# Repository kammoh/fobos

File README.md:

FOBOS
=====

Flexible Open-source workBench fOr Side-channel analysis (FOBOS) is an "acquisition to analysis" solution which includes all necessary software to control the device under test (attack) (DUT), trigger the oscilloscope, obtain the measurements and analyze them using several power analysis techniques.

FOBOS splits the Side Channel Analysis (SCA) setup into a control board, a DUT, and the SCA workstation. The firmware for the control board can be found in the folder `control`. The hardware description language files required to adapt a cryptographic algorithm to a particular FOBOS DUT are in the folder `DUT`. The `hardware` folder on the other hand contains circuit board design files for FOBOS boards such as the FOBOS Shield and several FOBOS DUTs. The `software` folder contains the scripts to run FOBOS. These python scripts run partially on the SCA workstation within a Jupyter notebook and partially on the Pynq DUT. The `docs` folder contains the FOBOS documentation.

FOBOS Control Board
-------------------
* `control`
   VHDL sources for configuring the FOBOS Control Boards. Requires Xilinx Vivado 2020.2.
   * `basys3ctrl`
     Using a Digilent Inc Basys 3 as control board and an oscilloscope for measurements.
   * `pynqctrl`
     Using a Digilent Inc PYNQ-Z1 as control board and either the FOBOS Shield or an oscilloscope for measurements.
   * `ip-repo` 
     Modules used by either control board.

FOBOS DUT
---------
* `dut`
  VHDL sources for FOBOS wrapper and pin assignments to prepare a DUT for instantiating a target algorithm.
  * `fpga_wrapper`
    Source code of the FOBOS wrapper common to all FPGA targets and the contraint files for the supported DUTs.
  * `soc_wrapper`
    Source code for system on chip boards such as Zybo.
  * `example_cores`
    Contains implementations of example algorithms required for the tutorials.
 
FOBOS Hardware
--------------
* `hardware`
  Printed Circuit Board design files for FOBOS boards. Requires KiCad.
  * `fobos-shield`
    FOBOS Shield is a data aqcuisition and benchmarking boad that can be attached to the PYNQ-Z1 controller.
  * `fobos-mtc`
    FOBOS Multi Target Connector allows simple connection of several DUT boards to the FOBOS Shield.
  * `fobos-dut`
    Contains folders for each FOBOS DUT.

FOBOS Software
--------------
* `software`
  FOBOS is controlled by a series of Python 3 scripts. They can be executed in several different ways.
  1. Command line, either on PYNQ or on a PC, tested on Windows 10 and Linux.
  1. Jupyter Notebook, either on PYNQ or on a PC, tested on Windows 10 and Linux.

  * `foboslib` contains all common FOBOS functions.
  * `notebooks` contains Jupyter notebooks that run within Jypyter Lab on a PC.
  * `pynq=notebooks` contains Jupyter notebooks that run on within Jupyter Hub on Pynq.
  * `examples` contains command line examples

Documentation
-------------

* `docs` 
  Contains the sources for the Sphinx based documentation of FOBOS and the makefile to compile it.
  All figures used for the FOBOS documentation are in the folder `docs\source\figures`.

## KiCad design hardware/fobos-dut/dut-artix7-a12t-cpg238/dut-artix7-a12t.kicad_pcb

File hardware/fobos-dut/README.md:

FOBOS-DUT Boards
=========
  * `dut-spartan7-s15`
    FOBOS DUT with a Xilinx Spartan-7 xc7s15cpga196-2 device and power measurement circuitry.
  * `dut-artix7-a12t-csg325`
    FOBOS DUT with a Xilinx Artix-7 xc7a12tcsg325 device and power measurement circuitry.
  * `dut-artix7-a12t-cpg238`
    FOBOS DUT with a Xilinx Artix-7 xc7a12tcpg238 device and power measurement circuitry.
  * `dut-cyclone10LP-016`
    FOBOS DUT with an Interl Cyclone 10 LP 10CL016-YU256C6 device and power measurement circuitry.
  * `dut-ecp5-25`
    FOBOS DUT with a Lattice ECP5 LFE5U-25F-6BG381C device and power measurement circuitry.

Check git Wiki

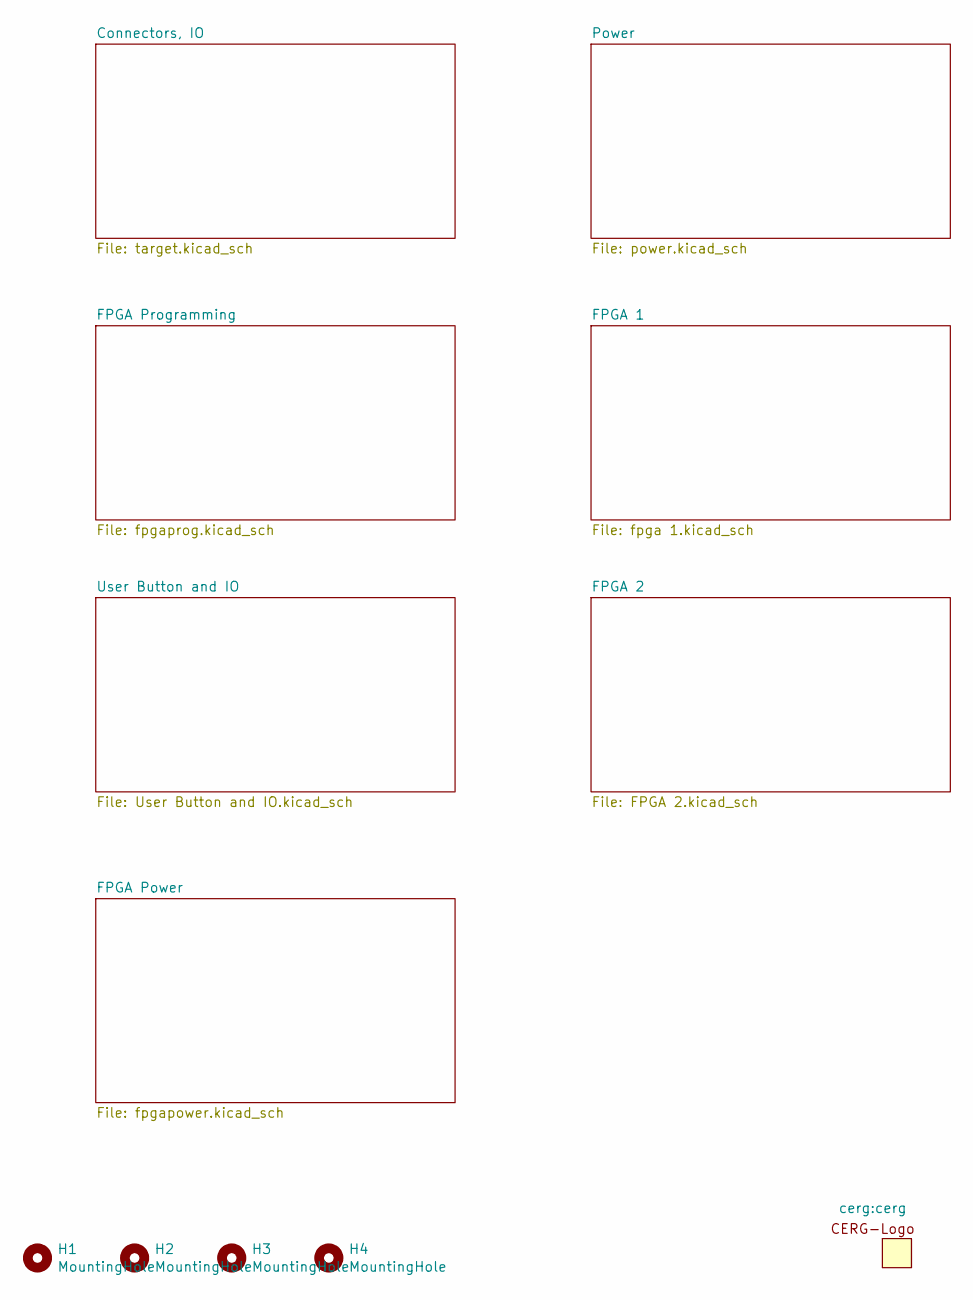
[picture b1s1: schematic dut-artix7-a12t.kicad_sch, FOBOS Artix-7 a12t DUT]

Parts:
H1, H2, H3, H4: MountingHole; MH_4-40

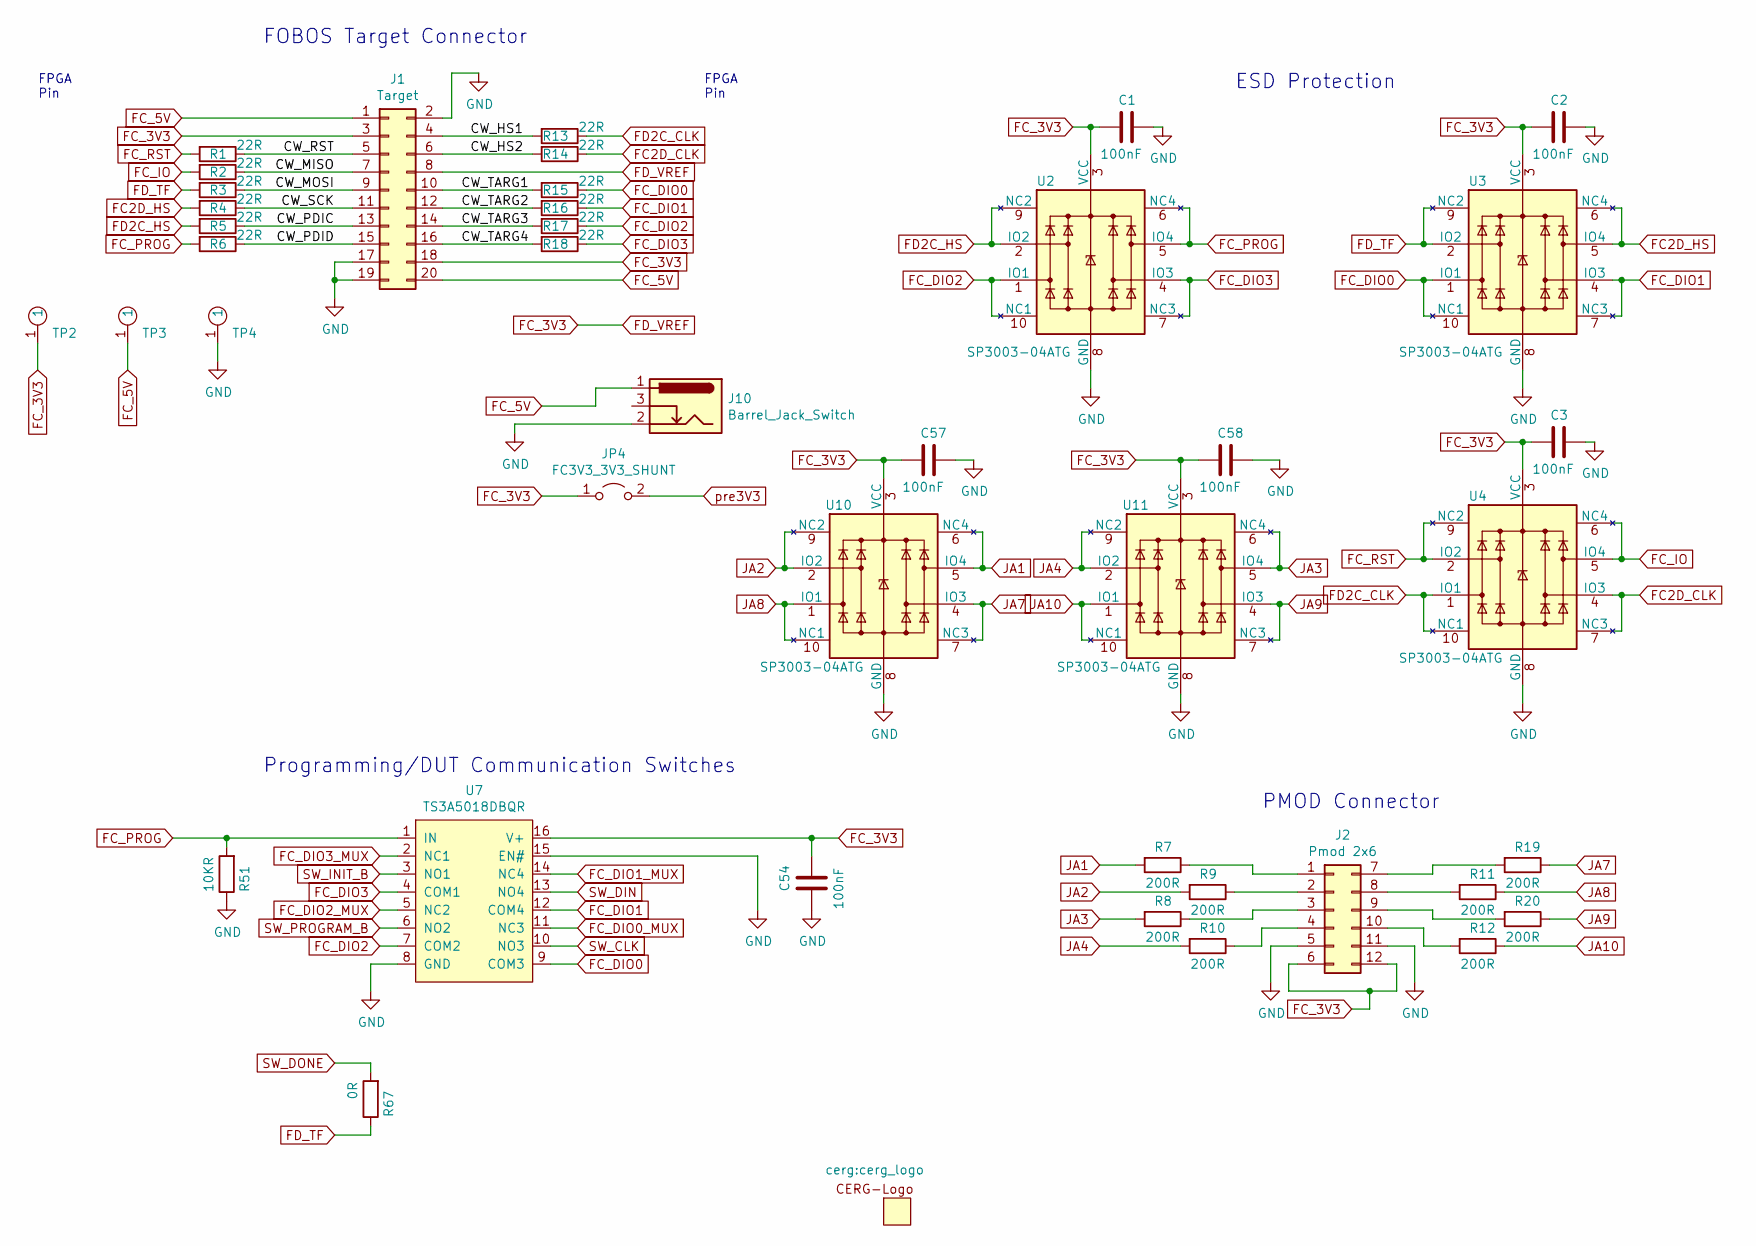
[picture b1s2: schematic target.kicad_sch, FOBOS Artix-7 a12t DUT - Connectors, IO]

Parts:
C1, C2, C3, C54, C57, C58: 100nF; C_0603_1608Metric; MPN 06036C104KAT4A
J1: Target; IDC-Header_2x10_P2.54mm_Horizontal; MPN 61202021721
J2: Pmod 2x6; PinSocket_2x06_P2.54mm_Horizontal_FLipped; MPN PH2RA-12-UA
J10: Barrel_Jack_Switch; BarrelJack_CUI_PJ-102AH_Horizontal
JP4: FC3V3_3V3_SHUNT; PinHeader_1x02_P2.54mm_Vertical; MPN 10129378-902001BLF
R1, R2, R3, R4, R5, R6, R13, R14, R15, R16, R17, R18: 22R; R_0603_1608Metric; MPN ERJ-U03J220V
R7, R8, R9, R10, R11, R12, R19, R20: 200R; R_0603_1608Metric; MPN ERA-3AED201V
R51: 10KR; R_0603_1608Metric; MPN ERJ-3EKF1002V
R67: 0R; R_0603_1608Metric; MPN RMCF0603ZT0R00
TP2, TP3, TP4: 5281; MPN 5281
U2, U3, U4, U10, U11: SP3003-04ATG; MSOP-10_3x3mm_P0.5mm; MPN SP3003-04ATG
U7: TS3A5018DBQR; SSOP-16_4.0x5.0mm_P0.635mm; MPN TS3A5018DBQR

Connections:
/Connectors, IO/CW_HS1: J1.4, R13.2
/Connectors, IO/CW_HS2: J1.6, R14.2
/Connectors, IO/CW_MISO: J1.7, R2.1
/Connectors, IO/CW_MOSI: J1.9, R3.1
/Connectors, IO/CW_PDIC: J1.13, R5.1
/Connectors, IO/CW_PDID: J1.15, R6.1
/Connectors, IO/CW_RST: J1.5, R1.1
/Connectors, IO/CW_SCK: J1.11, R4.1
/Connectors, IO/CW_TARG1: J1.10, R15.2
/Connectors, IO/CW_TARG2: J1.12, R16.2
/Connectors, IO/CW_TARG3: J1.14, R17.2
/Connectors, IO/CW_TARG4: J1.16, R18.2
FC2D_CLK: R14.1, U4.4 (IO3), U4.7 (NC3); also elsewhere on the board
FC2D_HS: R4.2, U3.5 (IO4), U3.6 (NC4); also elsewhere on the board
FC_5V: J1.1, J1.20, J10.1, TP3.1; also elsewhere on the board
FC_DIO0: R15.1, U3.1 (IO1), U3.10 (NC1), U7.9 (COM3)
FC_DIO0_MUX: U7.11 (NC3); also elsewhere on the board
FC_DIO1: R16.1, U3.4 (IO3), U3.7 (NC3), U7.12 (COM4)
FC_DIO1_MUX: U7.14 (NC4); also elsewhere on the board
FC_DIO2: R17.1, U2.1 (IO1), U2.10 (NC1), U7.7 (COM2)
FC_DIO2_MUX: U7.5 (NC2); also elsewhere on the board
FC_DIO3: R18.1, U2.4 (IO3), U2.7 (NC3), U7.4 (COM1)
FC_DIO3_MUX: U7.2 (NC1); also elsewhere on the board
FC_IO: R2.2, U4.5 (IO4), U4.6 (NC4); also elsewhere on the board
FC_PROG: R6.2, R51.2, U2.5 (IO4), U2.6 (NC4), U7.1 (IN)
FC_RST: R1.2, U4.2 (IO2), U4.9 (NC2); also elsewhere on the board
FD2C_CLK: R13.1, U4.1 (IO1), U4.10 (NC1); also elsewhere on the board
FD2C_HS: R5.2, U2.2 (IO2), U2.9 (NC2); also elsewhere on the board
FD_TF: R3.2, R67.1, U3.2 (IO2), U3.9 (NC2)
GND: C1.1, C2.1, C3.1, C54.2, C57.1, C58.1, J1.2, J1.17, J1.19, J2.5, J2.11, J10.2, R51.1, TP4.1, U2.8 (GND), U3.8 (GND), U4.8 (GND), U7.8 (GND), U7.15 (EN#), U10.8 (GND), U11.8 (GND); also elsewhere on the board
JA1: R7.2, U10.5 (IO4), U10.6 (NC4); also elsewhere on the board
JA2: R9.2, U10.2 (IO2), U10.9 (NC2); also elsewhere on the board
JA3: R8.2, U11.5 (IO4), U11.6 (NC4); also elsewhere on the board
JA4: R10.2, U11.2 (IO2), U11.9 (NC2); also elsewhere on the board
JA7: R19.1, U10.4 (IO3), U10.7 (NC3); also elsewhere on the board
JA8: R11.1, U10.1 (IO1), U10.10 (NC1); also elsewhere on the board
JA9: R20.1, U11.4 (IO3), U11.7 (NC3); also elsewhere on the board
JA10: R12.1, U11.1 (IO1), U11.10 (NC1); also elsewhere on the board
unnamed: J2.1, R7.1
unnamed: J2.2, R9.1
unnamed: J2.3, R8.1
unnamed: J2.4, R10.1
unnamed: J2.7, R19.2
unnamed: J2.8, R11.2
unnamed: J2.9, R20.2
unnamed: J2.10, R12.2
SW_CLK: U7.10 (NO3); also elsewhere on the board
SW_DIN: U7.13 (NO4); also elsewhere on the board
SW_DONE: R67.2; also elsewhere on the board
SW_INIT_B: U7.3 (NO1); also elsewhere on the board
SW_PROGRAM_B: U7.6 (NO2); also elsewhere on the board

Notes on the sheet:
Programming/DUT Communication Switches
FPGA Pin
ESD Protection
PMOD Connector
FOBOS Target Connector

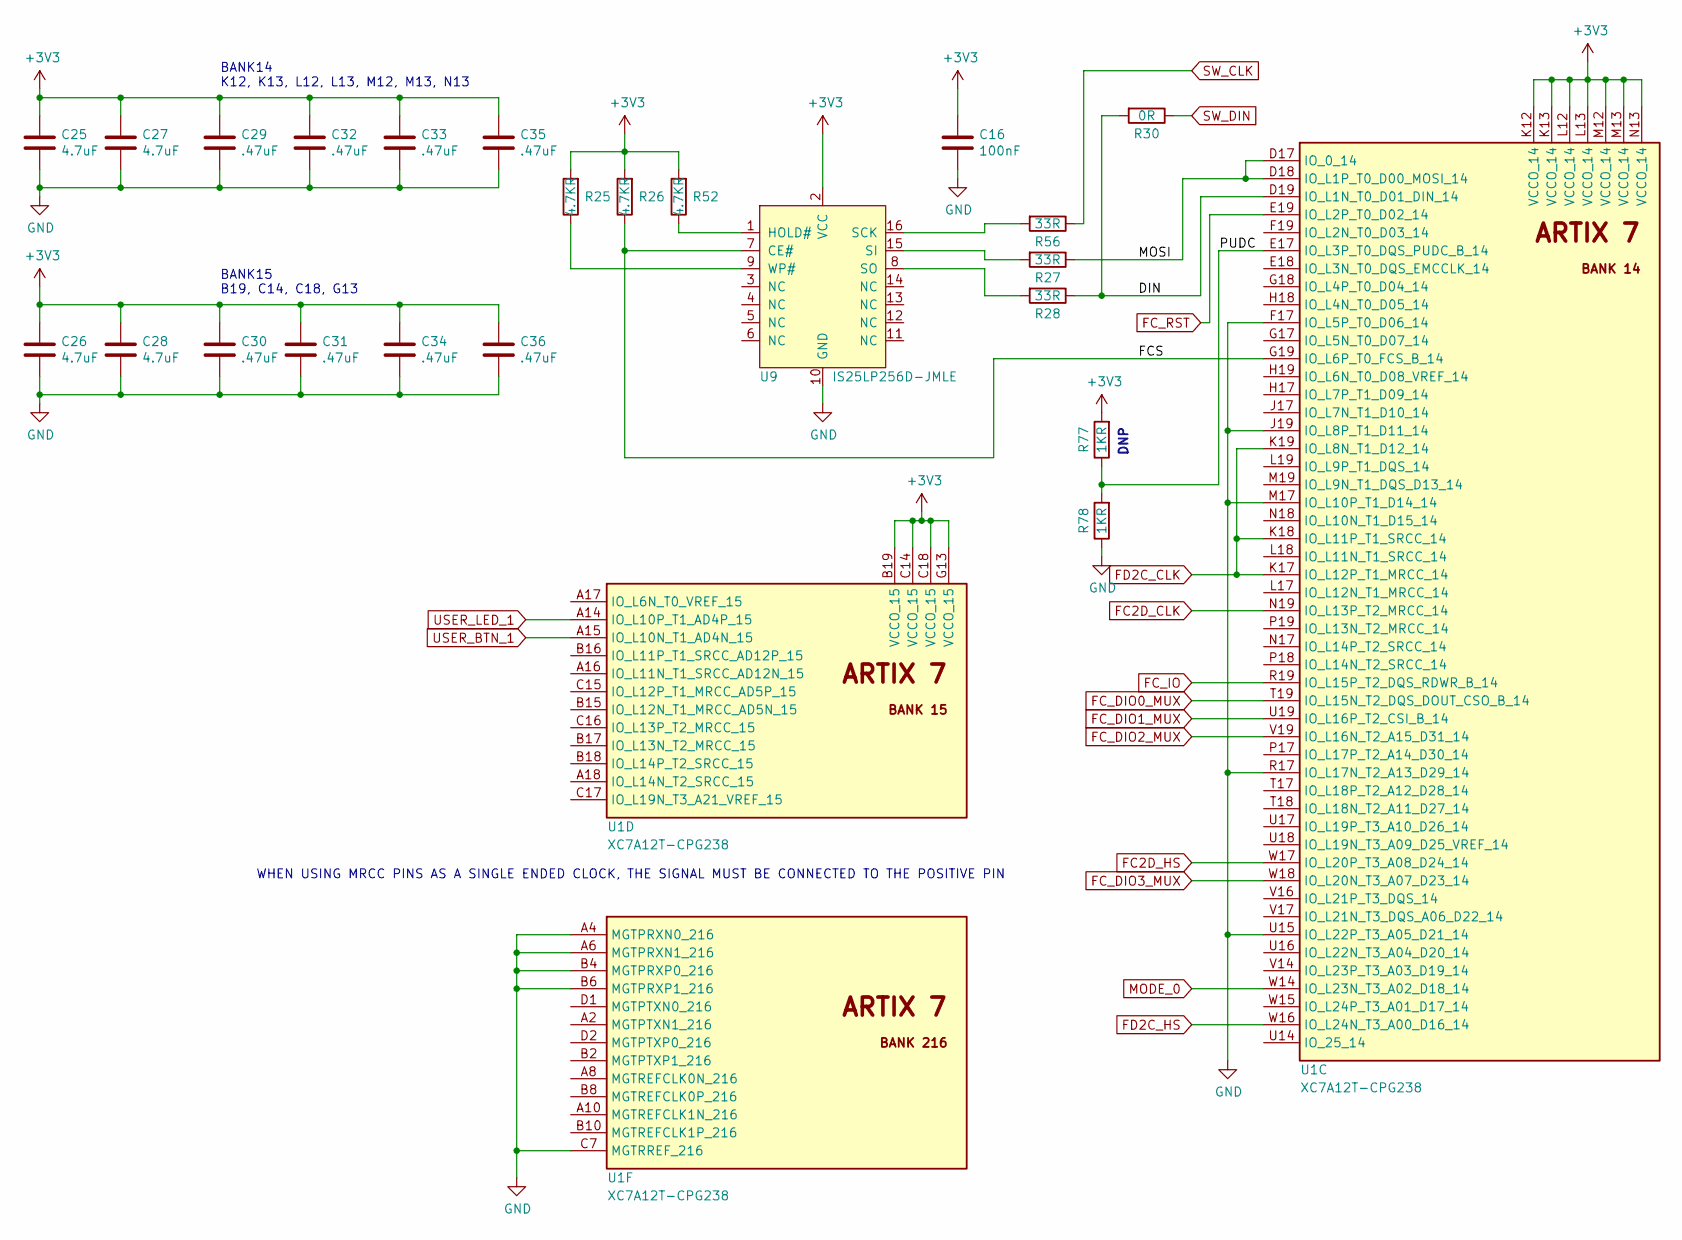
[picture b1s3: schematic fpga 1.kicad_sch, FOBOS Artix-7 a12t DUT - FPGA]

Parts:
C16: 100nF; C_0603_1608Metric; MPN 06036C104KAT4A
C25, C26, C27, C28: 4.7uF; C_0402_1005Metric_Pad0.74x0.62mm_HandSolder; MPN GRM155R60J475ME87J
C29, C30, C31, C32, C33, C34, C35, C36: .47uF; C_0402_1005Metric_Pad0.74x0.62mm_HandSolder; MPN C0402C474K9PACTU
R25, R26, R52: 4.7KR; R_0603_1608Metric; MPN ERJ-3GEYJ472V
R27, R28, R56: 33R; R_0603_1608Metric; MPN ERA-3AHD330V
R30: 0R; R_0603_1608Metric; MPN RMCF0603ZT0R00
R77, R78: 1KR; R_0603_1608Metric
U1: XC7A12T-CPG238; Xilinx_CPG238
U9: IS25LP256D-JMLE; SOIC-16W_7.5x10.3mm_P1.27mm; MPN IS25LP256D-JMLE

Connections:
/FPGA 1/DIN: R28.1, R30.2, U1.D19 (IO_L1N_T0_D01_DIN_14)
/FPGA 1/FCS: R26.1, U1.G19 (IO_L6P_T0_FCS_B_14), U9.7 (CE#)
/FPGA 1/MOSI: R27.1, U1.D17 (IO_0_14), U1.D18 (IO_L1P_T0_D00_MOSI_14)
/FPGA 1/PUDC: R77.1, R78.2, U1.E17 (IO_L3P_T0_DQS_PUDC_B_14)
FC2D_CLK: U1.N19 (IO_L13P_T2_MRCC_14); also elsewhere on the board
FC2D_HS: U1.W17 (IO_L20P_T3_A08_D24_14); also elsewhere on the board
FC_DIO0_MUX: U1.T19 (IO_L15N_T2_DQS_DOUT_CSO_B_14); also elsewhere on the board
FC_DIO1_MUX: U1.U19 (IO_L16P_T2_CSI_B_14); also elsewhere on the board
FC_DIO2_MUX: U1.V19 (IO_L16N_T2_A15_D31_14); also elsewhere on the board
FC_DIO3_MUX: U1.W18 (IO_L20N_T3_A07_D23_14); also elsewhere on the board
FC_IO: U1.R19 (IO_L15P_T2_DQS_RDWR_B_14); also elsewhere on the board
FC_RST: U1.E19 (IO_L2P_T0_D02_14); also elsewhere on the board
FD2C_CLK: U1.K17 (IO_L12P_T1_MRCC_14), U1.K18 (IO_L11P_T1_SRCC_14), U1.K19 (IO_L8N_T1_D12_14); also elsewhere on the board
FD2C_HS: U1.W16 (IO_L24N_T3_A00_D16_14); also elsewhere on the board
GND: C16.2, C25.2, C26.2, C27.2, C28.2, C29.2, C30.2, C31.2, C32.2, C33.2, C34.2, C35.2, C36.2, R78.1, U1.A4 (MGTPRXN0_216), U1.A6 (MGTPRXN1_216), U1.B4 (MGTPRXP0_216), U1.B6 (MGTPRXP1_216), U1.C7 (MGTRREF_216), U1.F17 (IO_L5P_T0_D06_14), U1.J19 (IO_L8P_T1_D11_14), U1.M17 (IO_L10P_T1_D14_14), U1.R17 (IO_L17N_T2_A13_D29_14), U1.U15 (IO_L22P_T3_A05_D21_14), U9.10 (GND); also elsewhere on the board
MODE_0: U1.W14 (IO_L23N_T3_A02_D18_14); also elsewhere on the board
unnamed: R25.1, U9.9 (WP#)
unnamed: R27.2, U9.15 (SI)
unnamed: R28.2, U9.8 (SO)
unnamed: R52.1, U9.1 (HOLD#)
unnamed: R56.2, U9.16 (SCK)
SW_CLK: R56.1; also elsewhere on the board
SW_DIN: R30.1; also elsewhere on the board
USER_BTN_1: U1.A15 (IO_L10N_T1_AD4N_15); also elsewhere on the board
USER_LED_1: U1.A14 (IO_L10P_T1_AD4P_15); also elsewhere on the board

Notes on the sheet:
WHEN USING MRCC PINS AS A SINGLE ENDED CLOCK, THE SIGNAL MUST BE CONNECTED TO THE POSITIVE PIN
DNP
BANK15 B19, C14, C18, G13
BANK14 K12, K13, L12, L13, M12, M13, N13

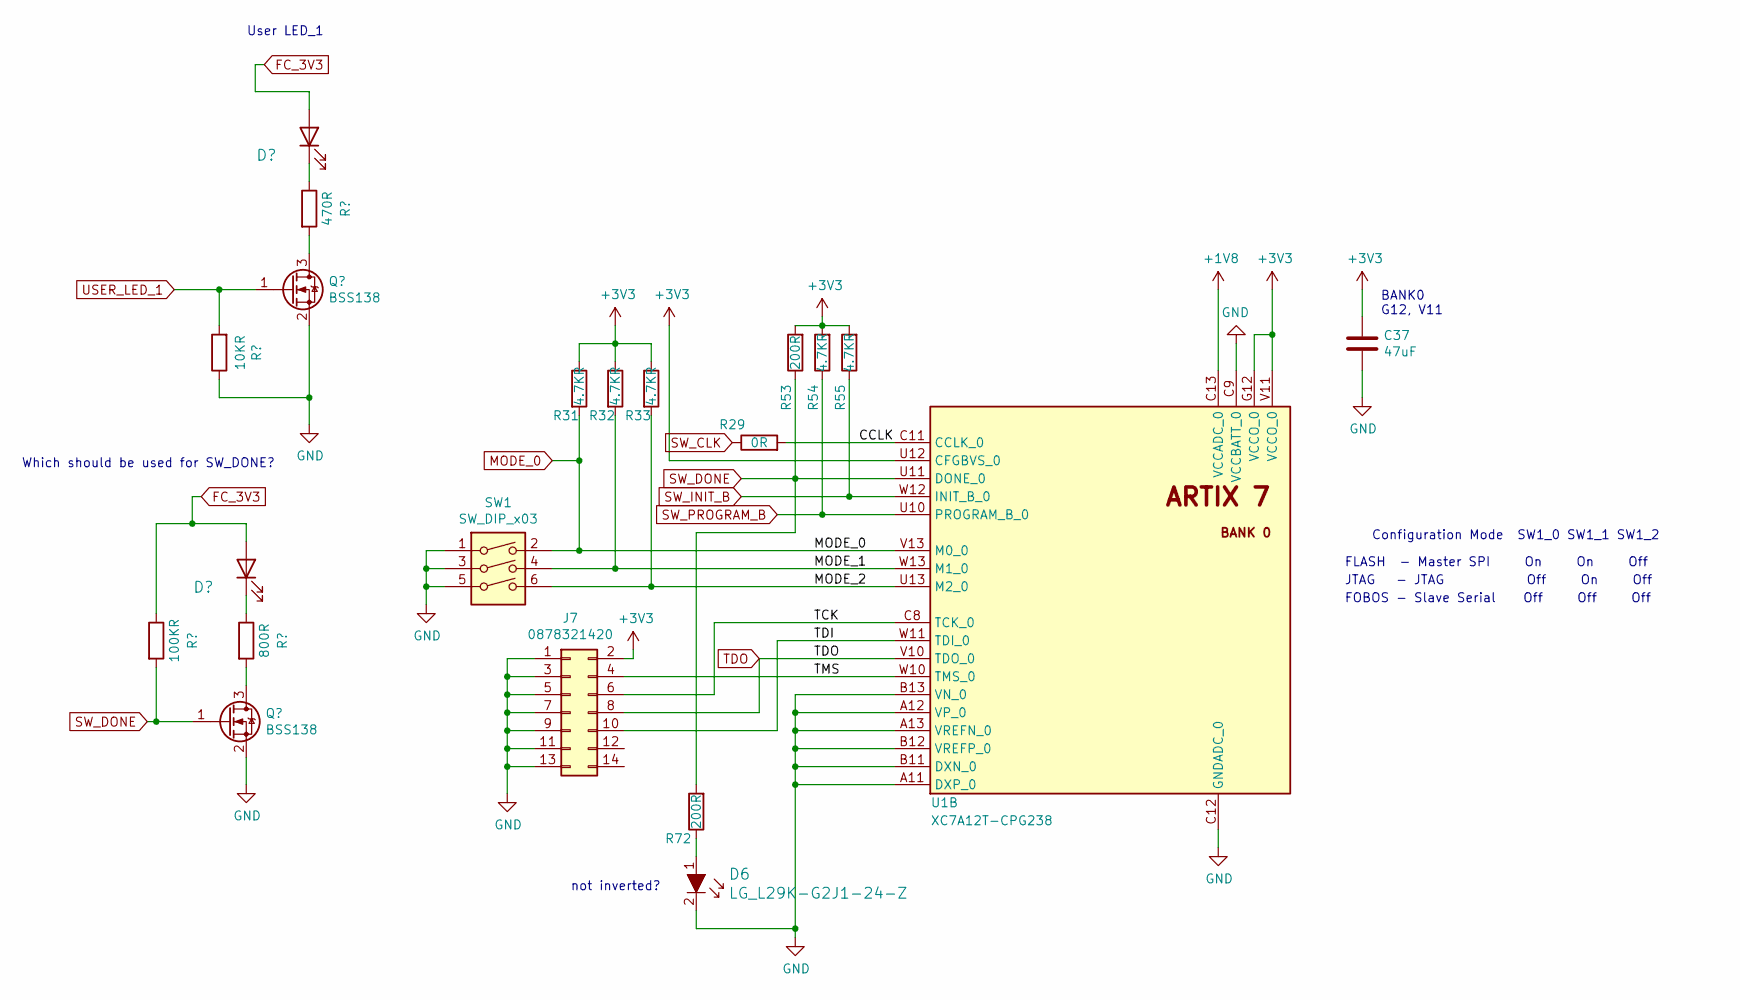
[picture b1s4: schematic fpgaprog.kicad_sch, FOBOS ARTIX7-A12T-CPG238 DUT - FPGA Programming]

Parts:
C37: 47uF; C_0603_1608Metric_Pad1.08x0.95mm_HandSolder; MPN 06036D476MAT2A
D6: LG_L29K-G2J1-24-Z; LED_0603_1608Metric; MPN LG L29K-G2J1-24-Z; Digi-Key_PN 475-2709-1-ND
J7: 0878321420; PinHeader_2x7_P2mm_SMD; MPN 0878321420; Digi-Key_PN WM18641-ND
R29: 0R; R_0603_1608Metric; MPN RMCF0603ZT0R00
R31, R32, R33, R54, R55: 4.7KR; R_0603_1608Metric; MPN ERJ-3GEYJ472V
R53, R72: 200R; R_0603_1608Metric; MPN ERA-3AED201V
SW1: SW_DIP_x03; DS04-254-2-03BK-SMT; MPN DS04-254-2-03BK-SMT
U1: XC7A12T-CPG238; Xilinx_CPG238

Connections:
/FPGA Programming/CCLK: R29.2, U1.C11 (CCLK_0)
/FPGA Programming/MODE_1: R32.2, SW1.4, U1.W13 (M1_0)
/FPGA Programming/MODE_2: R33.2, SW1.6, U1.U13 (M2_0)
/FPGA Programming/TCK: J7.6, U1.C8 (TCK_0)
/FPGA Programming/TDI: J7.10, U1.W11 (TDI_0)
/FPGA Programming/TMS: J7.4, U1.W10 (TMS_0)
GND: C37.2, D6.2, J7.1, J7.3, J7.5, J7.7, J7.9, J7.11, J7.13, SW1.1, SW1.3, SW1.5, U1.A11 (DXP_0), U1.A12 (VP_0), U1.A13 (VREFN_0), U1.B11 (DXN_0), U1.B12 (VREFP_0), U1.B13 (VN_0), U1.C9 (VCCBATT_0), U1.C12 (GNDADC_0); also elsewhere on the board
MODE_0: R31.2, SW1.2, U1.V13 (M0_0); also elsewhere on the board
unnamed: D6.1, R72.1
SW_CLK: R29.1; also elsewhere on the board
SW_DONE: R53.1, R72.2, U1.U11 (DONE_0); also elsewhere on the board
SW_INIT_B: R55.1, U1.W12 (INIT_B_0); also elsewhere on the board
SW_PROGRAM_B: R54.1, U1.U10 (PROGRAM_B_0); also elsewhere on the board
TDO: J7.8, U1.V10 (TDO_0); also elsewhere on the board

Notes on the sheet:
BANK0 G12, V11
not inverted?
JTAG - JTAG Off On Off
FLASH - Master SPI On On Off
FOBOS - Slave Serial Off Off Off
Which should be used for SW_DONE?
Configuration Mode SW1_0 SW1_1 SW1_2
User LED_1

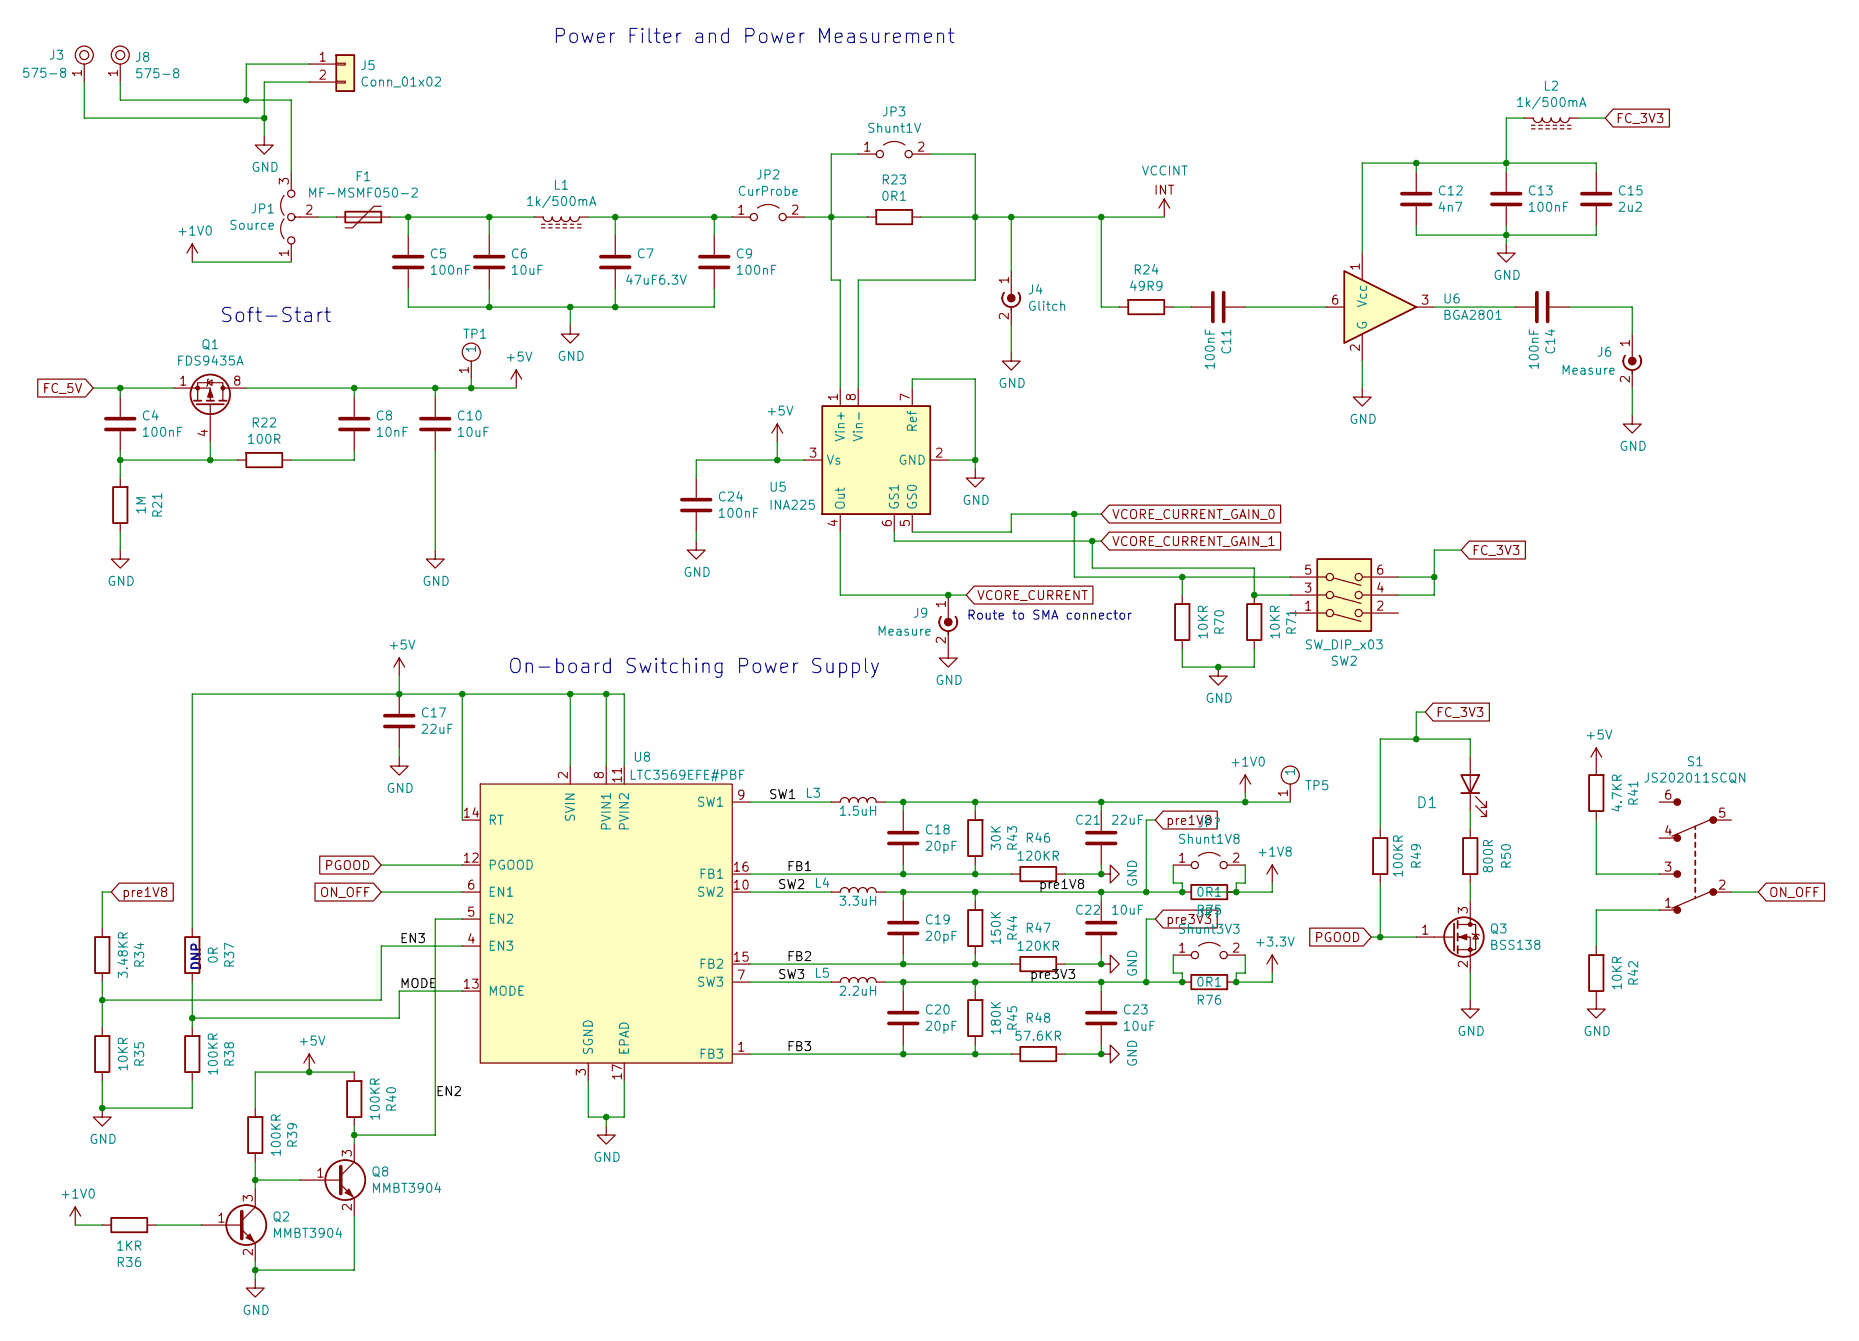
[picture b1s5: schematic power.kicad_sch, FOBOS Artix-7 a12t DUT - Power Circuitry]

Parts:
C4, C5, C9, C11, C13, C14, C24: 100nF; C_0603_1608Metric; MPN 06036C104KAT4A
C6, C10, C22, C23: 10uF; C_0805_2012Metric; MPN GRM21BR70J106KA73L
C7: 47uF6.3V; C_0805_2012Metric; Part GRM21BR60J476ME15K
C8: 10nF; C_0603_1608Metric; MPN 885012206014
C12: 4n7; C_0603_1608Metric; MPN 885012206012
C15: 2u2; C_0805_2012Metric; MPN 885012207001
C17, C21: 22uF; C_0805_2012Metric; MPN CL21A226KQCLRNC
C18, C19, C20: 20pF; C_0603_1608Metric; MPN C0603C200G8HAC7867
D1: LG_L29K-G2J1-24-Z; LED_0603_1608Metric; MPN LG L29K-G2J1-24-Z; Digi-Key_PN 475-2709-1-ND
F1: MF-MSMF050-2; Fuse_1206_3216Metric; MPN ERB-RG2R00V
J3, J8: 575-8; MPN 575-8
J4: Glitch; SMA-JOHNSON-142-0701-201; MPN 142-0701-801
J5: Conn_01x02; Molex_KK-254_AE-6410-02A_1x02_P2.54mm_Vertical; MPN 0022272021
J6, J9: Measure; SMA-JOHNSON-142-0701-801; MPN 142-0701-801
JP1: Source; PinHeader_1x03_P2.54mm_Vertical; MPN 77311-822-03LF
JP2: CurProbe; PinHeader_1x02_P2.54mm_Vertical; MPN 10129378-902001BLF
JP3: Shunt1V; PinHeader_1x02_P2.54mm_Vertical; MPN 10129378-902001BLF
L1, L2: 1k/500mA; L_0603_1608Metric
L3: 1.5uH; L_SRN2012; MPN SRN2012-1R5M
L4: 3.3uH; L_BRC2012; MPN BRC2012T3R3MD
L5: 2.2uH; L_SRN2012; MPN SRN2010-2R2M
Q1: FDS9435A; SOIC-8_3.9x4.9mm_P1.27mm; MPN FDS9435A
Q2, Q8: MMBT3904; SOT-23
Q3: BSS138; SOT-23; MPN BSS138
R21: 1M; R_0603_1608Metric; MPN ERJ-3GEYJ105V
R22: 100R; R_0603_1608Metric; MPN ERJ-U03J101V
R23: 0R1; R_1206_3216Metric; MPN KRL1632E-M-R100-F-T5
R24: 49R9; R_0603_1608Metric; MPN ERJ-3EKF49R9V
R34: 3.48KR; R_0603_1608Metric; MPN ERJ-3EKF3481V
R35, R42, R70, R71: 10KR; R_0603_1608Metric; MPN ERJ-3EKF1002V
R36: 1KR; R_0603_1608Metric; MPN ERA-3AED102V
R37: 0R; R_0603_1608Metric; MPN RMCF0603ZT0R00
R38, R39, R40, R49: 100KR; R_0603_1608Metric; MPN ERA-3AED104V
R41: 4.7KR; R_0603_1608Metric; MPN ERJ-3GEYJ472V
R43: 30K; R_0603_1608Metric; MPN ERJ-3EKF1002V
R44: 150K; R_0603_1608Metric; MPN ERJ-3EKF1002V
R45: 180K; R_0603_1608Metric; MPN ERJ-3EKF1002V
R46, R47: 120KR; R_0603_1608Metric; MPN ERJ-3EKF1203V
R48: 57.6KR; R_0603_1608Metric; MPN ERJ-3EKF5762V
R50: 800R; R_0603_1608Metric; MPN RC0603FR-07806RL
R75, R76: 0R1; R_1206_3216Metric
S1: JS202011SCQN; Switch_Slide_JS202011SCQN; MPN JS202011SCQN; Digi-Key_PN 401-2002-1-ND
SW2: SW_DIP_x03; DS04-254-2-03BK-SMT; MPN DS04-254-2-03BK-SMT
TP1, TP5: 5281; MPN 5281
U5: INA225; MSOP-8_3x3mm_P0.65mm; MPN INA225AIDGKT
U6: BGA2801; SOT-363_SC-70-6; MPN BGA2801,115
U8: LTC3569EFE#PBF; TSSOP-16-1EP_W4.40mm; MPN LTC3569EFE#PBF

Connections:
+1V0: C18.1, C21.1, JP1.1 (A), L3.2, R36.1, R43.2, TP5.1
+5V: C8.1, C10.1, C17.1, Q1.5 (D), Q1.6 (D), Q1.7 (D), Q1.8 (D), R37.2, R39.2, R40.2, R41.2, TP1.1, U8.2 (SVIN), U8.8 (PVIN1), U8.11 (PVIN2), U8.14 (RT)
/Power/EN2: Q8.3 (C), R40.1, U8.5 (EN2)
/Power/EN3: R34.1, R35.2, U8.4 (EN3)
/Power/FB1: C18.2, R43.1, R46.1, U8.16 (FB1)
/Power/FB2: C19.2, R44.1, R47.1, U8.15 (FB2)
/Power/FB3: C20.2, R45.1, R48.1, U8.1 (FB3)
/Power/MODE: R37.1, R38.2, U8.13 (MODE)
/Power/SW1: L3.1, U8.9 (SW1)
/Power/SW2: L4.1, U8.10 (SW2)
/Power/SW3: L5.1, U8.7 (SW3)
/Power/pre3V3: C20.1, C23.1, L5.2, R45.2, R76.1; also elsewhere on the board
FC_5V: C4.1, Q1.1 (S), Q1.2 (S), Q1.3 (S); also elsewhere on the board
GND: C5.2, C6.2, C7.2, C9.2, C10.2, C12.2, C13.2, C15.2, C17.2, C21.2, C22.2, C23.2, C24.2, J3.1, J4.2 (Ext), J5.2, J6.2 (Ext), J9.2 (Ext), Q2.2 (E), Q3.2 (S), Q8.2 (E), R21.1, R35.1, R38.1, R42.1, R46.2, R47.2, R48.2, R70.1, R71.1, U5.2 (GND), U5.7 (Ref), U6.2 (G), U6.4 (G), U6.5 (G), U8.3 (SGND), U8.17 (EPAD); also elsewhere on the board
unnamed: C4.2, Q1.4 (G), R21.2, R22.2
unnamed: C5.1, C6.1, F1.1, L1.2
unnamed: C7.1, C9.1, JP2.1 (A), L1.1
unnamed: C8.2, R22.1
unnamed: C11.1, U6.6
unnamed: C11.2, R24.1
unnamed: C12.1, C13.1, C15.1, L2.2, U6.1 (Vcc)
unnamed: C14.1, J6.1 (In)
unnamed: C14.2, U6.3
unnamed: D1.1 (K), R50.1
unnamed: F1.2, JP1.2 (C)
unnamed: J5.1, J8.1, JP1.3 (B)
unnamed: JP2.2 (B), JP3.1 (A), R23.2, U5.1 (Vin+)
unnamed: Q2.1 (B), R36.2
unnamed: Q2.3 (C), Q8.1 (B), R39.1
unnamed: Q3.3 (D), R50.2
unnamed: R41.1, S1.3
unnamed: R42.2, S1.1
ON_OFF: S1.2, U8.6 (EN1)
PGOOD: Q3.1 (G), R49.2, U8.12 (PGOOD)
VCCINT: J4.1 (In), JP3.2 (B), R23.1, R24.2, U5.8 (Vin-); also elsewhere on the board
VCORE_CURRENT: J9.1 (In), U5.4 (Out)
VCORE_CURRENT_GAIN_0: R70.2, SW2.5, U5.5 (GS0); also elsewhere on the board
VCORE_CURRENT_GAIN_1: R71.2, SW2.3, U5.6 (GS1); also elsewhere on the board

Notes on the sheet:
DNP
On-board Switching Power Supply
Route to SMA connector
Soft-Start
Power Filter and Power Measurement

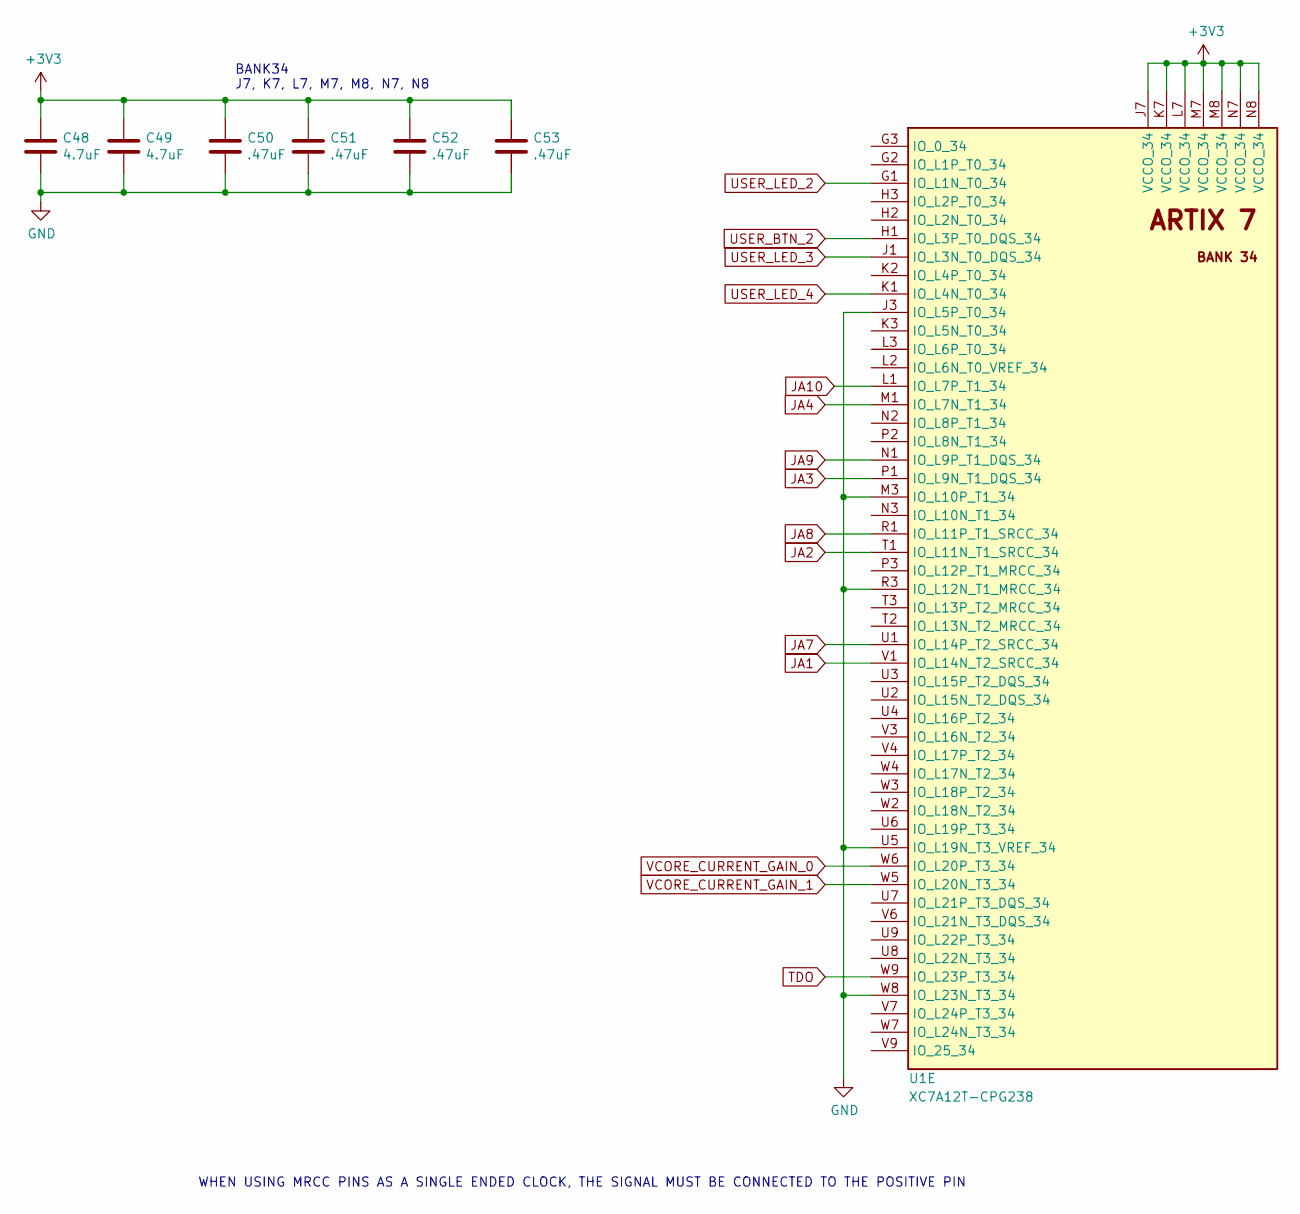
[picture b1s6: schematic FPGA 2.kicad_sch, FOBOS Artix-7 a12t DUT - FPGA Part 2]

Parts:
C48, C49: 4.7uF; C_0402_1005Metric_Pad0.74x0.62mm_HandSolder; MPN GRM155R60J475ME87J
C50, C51, C52, C53: .47uF; C_0402_1005Metric_Pad0.74x0.62mm_HandSolder; MPN C0402C474K9PACTU
U1: XC7A12T-CPG238; Xilinx_CPG238

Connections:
GND: C48.2, C49.2, C50.2, C51.2, C52.2, C53.2, U1.J3 (IO_L5P_T0_34), U1.M3 (IO_L10P_T1_34), U1.R3 (IO_L12N_T1_MRCC_34), U1.U5 (IO_L19N_T3_VREF_34), U1.W8 (IO_L23N_T3_34); also elsewhere on the board
JA1: U1.V1 (IO_L14N_T2_SRCC_34); also elsewhere on the board
JA2: U1.T1 (IO_L11N_T1_SRCC_34); also elsewhere on the board
JA3: U1.P1 (IO_L9N_T1_DQS_34); also elsewhere on the board
JA4: U1.M1 (IO_L7N_T1_34); also elsewhere on the board
JA7: U1.U1 (IO_L14P_T2_SRCC_34); also elsewhere on the board
JA8: U1.R1 (IO_L11P_T1_SRCC_34); also elsewhere on the board
JA9: U1.N1 (IO_L9P_T1_DQS_34); also elsewhere on the board
JA10: U1.L1 (IO_L7P_T1_34); also elsewhere on the board
TDO: U1.W9 (IO_L23P_T3_34); also elsewhere on the board
USER_BTN_2: U1.H1 (IO_L3P_T0_DQS_34); also elsewhere on the board
USER_LED_2: U1.G1 (IO_L1N_T0_34); also elsewhere on the board
USER_LED_3: U1.J1 (IO_L3N_T0_DQS_34); also elsewhere on the board
USER_LED_4: U1.K1 (IO_L4N_T0_34); also elsewhere on the board
VCORE_CURRENT_GAIN_0: U1.W6 (IO_L20P_T3_34); also elsewhere on the board
VCORE_CURRENT_GAIN_1: U1.W5 (IO_L20N_T3_34); also elsewhere on the board

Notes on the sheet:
BANK34 J7, K7, L7, M7, M8, N7, N8
WHEN USING MRCC PINS AS A SINGLE ENDED CLOCK, THE SIGNAL MUST BE CONNECTED TO THE POSITIVE PIN

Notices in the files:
control/pynqctrl/vivado/src/constr/pynq_rev2.xdc:
Copyright 2021 CERG
Licensed under the Apache License, Version 2.0 (the "License");
sources/pynq_controller/vivado/src/constr/pynq.xdc:
Copyright 2019 CERG
hardware/fobos-dut/dut-artix7-a12t-cpg238/FPGA 2.kicad_sch:
License: Apache License Version 2.0
Copyright © Cryptographic Engineering Research Group
